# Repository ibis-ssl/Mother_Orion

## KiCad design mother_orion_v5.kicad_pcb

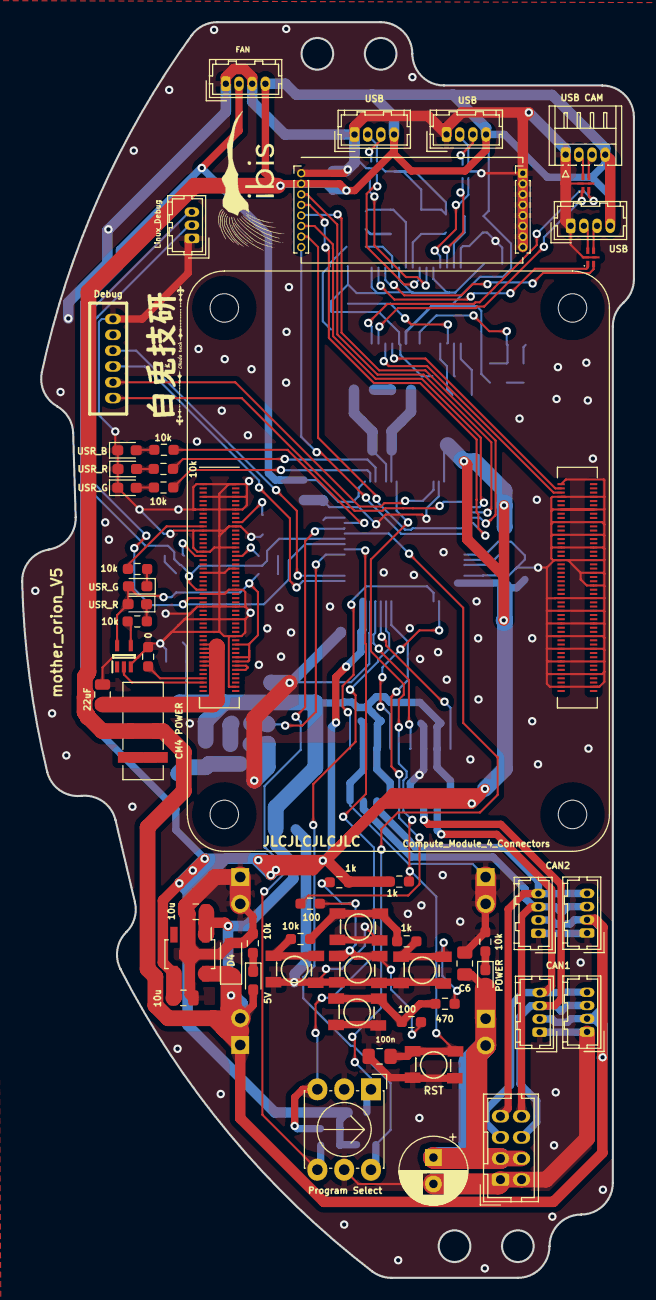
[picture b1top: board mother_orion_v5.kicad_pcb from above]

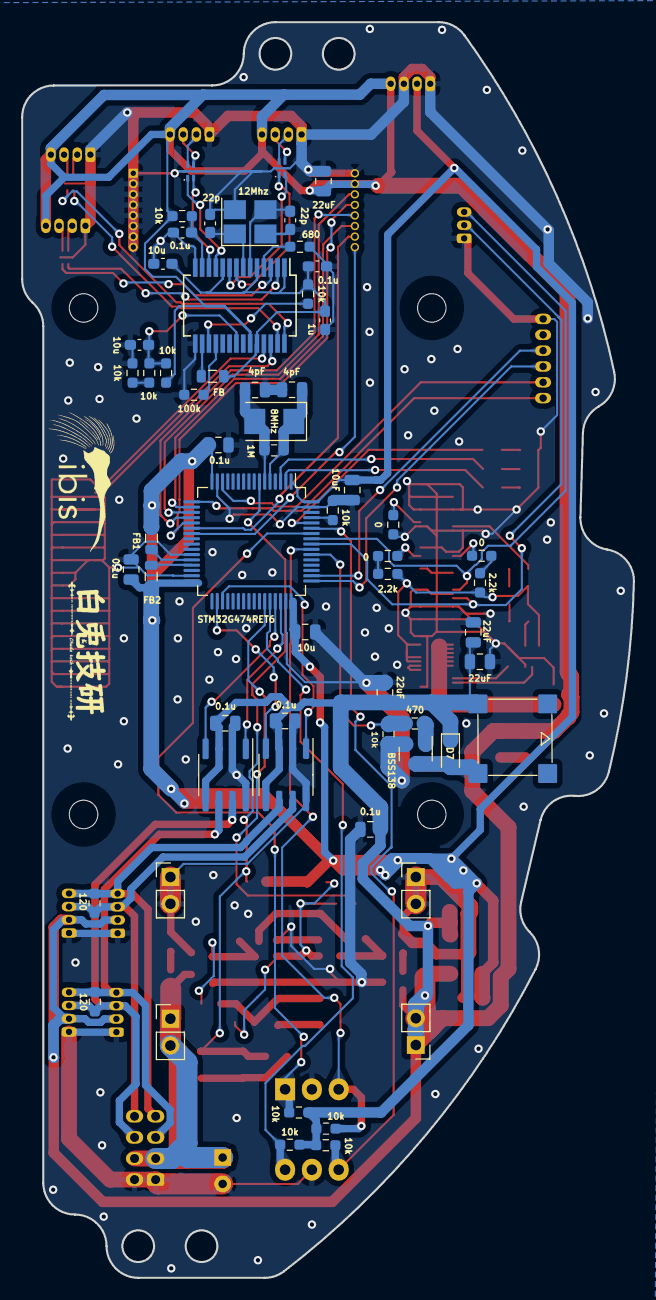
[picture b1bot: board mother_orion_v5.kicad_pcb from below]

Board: 2 copper layers, 58.0 x 119.0 mm, 119 parts (61 on the bottom side), 94 nets.

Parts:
8MHz: Crystal; Crystal_SMD_5032-2Pin_5.0x3.2mm
12Mhz: 12MHz; Crystal_SMD_3225-4Pin_3.2x2.5mm_HandSoldering
 : CAN1_EXT; Hirose_DF13-04P-1.25DSA_1x04_P1.25mm_Vertical
 #2: CAN1_EXT; Hirose_DF13-04P-1.25DSA_1x04_P1.25mm_Vertical
 #3: L_BTN; SW_
 #4,  #23: ibis_logo_mid
 #5: T_BTN; SW_
 #6,  #11: CAN2_EXT; Hirose_DF13-04P-1.25DSA_1x04_P1.25mm_Vertical
 #7: 56uF25V; CP_Radial_D6.3mm_P2.50mm
 #8,  #10,  #21,  #22: LXES11D; FIL_LXES11DAA2-135
 #9: B_BTN; SW_
 #12: Conn_02x04_Odd_Even; Hirose_DF11-8DP-2DSA_2x04_P2.00mm_Vertical
 #13: R_BTN; SW_
 #14,  #17: PinHeader_1x08_P1.00mm_Vertical
 #15: NJM2884U1-33; SOT-89-5
 #16,  #26: sirousagikenn_mini
 #18: 74LVC1G07; SOT65P212X110-5N
 #19: C_BTN; SW_
 #20,  #24,  #25,  #27: power; PinHeader_1x02_P2.54mm_Vertical
 #28,  #30: TCAN1051GDRQ1; SOIC-8_3.9x4.9mm_P1.27mm
 #29: SSOP-28_5.3x10.2mm_P0.65mm
C1, C4, C10: 10u; C_0805_2012Metric
C2: 10uF; C_0805_2012Metric
C3, C5, C7, C12, C12#2: 0.1u; C_0805_2012Metric
C6: 22uF; C_0805_2012Metric_Pad1.18x1.45mm_HandSolder
C14: 100n; C_0805_2012Metric_Pad1.18x1.45mm_HandSolder
C15, C16, C16#2, C16#3, C17: 22uF; C_0805_2012Metric
C18, C19: 4pF; C_0805_2012Metric
C20, C21: 22p; C_0603_1608Metric_Pad1.08x0.95mm_HandSolder
C22, C24: 0.1u; C_0603_1608Metric_Pad1.08x0.95mm_HandSolder
C23, C26: 10u; C_0603_1608Metric_Pad1.08x0.95mm_HandSolder
C25: 1u; C_0603_1608Metric_Pad1.08x0.95mm_HandSolder
CM4 POWER: SW_DPDT_x2; SW_DPDT_CK_JS202011JCQN
D2: 5V; LED_0603_1608Metric_Pad1.05x0.95mm_HandSolder
D3: USR_B; LED_0603_1608Metric_Pad1.05x0.95mm_HandSolder
D4: 5.6V; D_SOD-123
D5, D8: USR_G; LED_0603_1608Metric_Pad1.05x0.95mm_HandSolder
D6, D9: USR_R; LED_0603_1608Metric_Pad1.05x0.95mm_HandSolder
D7: D; D_SOD-323_HandSoldering
FB, FB1, FB2: 600R@100MHz; L_0805_2012Metric
J10: Linux_Debug; Hirose_DF13-03P-1.25DSA_1x03_P1.25mm_Vertical
J11: USB CAM; Hirose_DF13-04P-1.25DS_1x04_P1.25mm_Horizontal
J13: Debug; ZH_6T
J14: FAN; Hirose_DF13-04P-1.25DSA_1x04_P1.25mm_Vertical
POWER: PWR; LED_0603_1608Metric_Pad1.05x0.95mm_HandSolder
Program Select: SW_Coded_SH-7050; Nidec_Copal_SH-7010C
Q1: BSS138; SOT-23
R1, R3, R4, R5, R7, R9, R13, R19, R20, R22, R23, R24, R25, R26, R27, R28, R34, R35, R36: 10k; R_0603_1608Metric_Pad0.98x0.95mm_HandSolder
R2, R6: 120; R_0603_1608Metric_Pad0.98x0.95mm_HandSolder
R8, R12, R17: 1k; R_0603_1608Metric_Pad0.98x0.95mm_HandSolder
R10, R14: 470; R_0603_1608Metric_Pad0.98x0.95mm_HandSolder
R11, R15: 100; R_0603_1608Metric_Pad0.98x0.95mm_HandSolder
R16, R31: 2.2k; R_0603_1608Metric_Pad0.98x0.95mm_HandSolder
R18, R21, R29, R30: 0; R_0603_1608Metric_Pad0.98x0.95mm_HandSolder
R32: 1M; R_0603_1608Metric_Pad0.98x0.95mm_HandSolder
R33: 100k; R_0603_1608Metric_Pad0.98x0.95mm_HandSolder
R37: 680; R_0603_1608Metric_Pad0.98x0.95mm_HandSolder
RST: nRST; SW_
U2: STM32G474RET6; LQFP-64_10x10mm_P0.5mm
U3: Compute_Module_4_Connectors; Raspberry-Pi-4-Compute-Module
USB: USB2.0; Hirose_DF13-04P-1.25DSA_1x04_P1.25mm_Vertical
USB#2, USB#3: USB2.0; Hirose_DF13-04P-1.25DSA_1x04_P1.25mm_Vertical

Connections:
+1V8: U3.88 (CM4_1.8V_Out), U3.90 (CM4_1.8V_Out)
+3.3VA: #18.5 (VCC), D8.2 (A), D9.2 (A), R16.2, R31.2, U3.78 (GPIO_VREF), U3.84 (CM4_3.3V_Out), U3.86 (CM4_3.3V_Out)
+3V3: #15.4 (VOUT), C1.1, C2.1, C3.1, C7.1, C10.1, FB1.2, FB2.2, J14.2, R12.1, R17.1, R24.1, R25.1, R26.1, R27.1, U2.1 (VBAT), U2.16 (VDD), U2.32 (VDD), U2.48 (VDD), U2.64 (VDD)
+5V: .2, #2.2, #6.2, #11.2, #14.2, #15.1 (CTRL), #15.5 (VIN), #25.1, #25.2, #28.3 (VCC), #28.5 (NC), #29.23 (V5), #30.3 (VCC), #30.5 (NC), C4.1, C5.1, C12.1, C12#2.1, C15.1, C16#2.1, C16#3.1, C17.1, CM4 POWER.2 (B), CM4 POWER.5 (B), D2.2 (A), D4.1 (A1), D7.1 (K), J11.4, J14.4, R22.1, R36.2, USB.4, USB#2.4, USB#3.4
+BATT: #7.1, #12.3, #12.4, #20.1, #20.2, C6.1, POWER.2 (A)
/CM4_RX: J10.3, U2.57 (PB4), U3.51 (GPIO15)
/CM4_TX: J10.2, U2.56 (PB3), U3.55 (GPIO14)
/DIP_0: Program Select.1, R24.2, U2.58 (PB5)
/DIP_1: Program Select.2, R25.2, U2.59 (PB6)
/DIP_2: Program Select.4, R26.2, U2.55 (PD2)
/DIP_3: Program Select.8, R27.2, U2.44 (PA10)
/IMU_FSYNC: #14.8, U2.23 (PC5)
/IMU_INT: #14.7, U2.22 (PC4)
/LED_B: R4.2, U2.60 (PB7)
/LED_G: R7.2, U2.2 (PC13)
/LED_R: R9.2, U2.3 (OSC32_IN-PC14)
/SCD1: R30.2, R31.1
/SCL1: R16.1, R18.2
/SPI_IMU_CS: #14.6, U2.18 (PA4)
/SPI_MISO: #14.5, U2.20 (PA6)
/SPI_MOSI: #14.4, U2.21 (PA7)
/SPI_SCLK: #14.3, U2.19 (PA5)
/STLK_RX: J13.6, U2.17 (PA3)
/STLK_TX: J13.5, U2.14 (PA2)
/T_NRST: C14.1, R17.2, RST.2, U2.7 (NRST-PG10)
/T_TCK: J13.3, U2.50 (PA14)
/T_TMS: J13.4, U2.49 (PA13)
/U_BTN: R15.1, U2.43 (PA9)
Buzzer: R13.2, R14.2, U2.54 (PC12)
CAN1_H: .3, #2.3, #12.6, #28.7 (CANH), R2.1
CAN1_L: .4, #2.4, #12.5, #28.6 (CANL), R2.2
CAN1_RXD: #28.4 (RXD), U2.45 (PA11)
CAN1_TXD: #28.1 (TXD), U2.46 (PA12)
CAN2_H: #6.3, #11.3, #12.8, #30.7 (CANH), R6.1
CAN2_L: #6.4, #11.4, #12.7, #30.6 (CANL), R6.2
CAN2_RXD: #30.4 (RXD), U2.34 (PB12)
CAN2_TXD: #30.1 (TXD), U2.35 (PB13)
GND: 12Mhz.2, 12Mhz.4, .1, #2.1, #3.1, #5.1, #6.1, #7.2, #8.3, #8.6, #9.1, #10.3, #10.6, #11.1, #12.1, #12.2, #13.1, #14.1, #15.2 (GND), #17.1, #17.2, #17.3, #17.4, #17.5, #17.6, #17.7, #17.8, #18.3 (GND), #19.1, #21.3, #21.6, #22.3, #22.6, #24.1, #24.2, #27.1, #27.2, #28.2 (GND), #28.8 (S), #29.14 (TEST), #29.15 (GND), #30.2 (GND), #30.8 (S), C1.2, C2.2, C3.2, C4.2, C5.2, C6.2, C7.2, C10.2, C12.2, C12#2.2, C14.2, C15.2, C16.1, C16#2.2, C16#3.2, C17.2, C18.1, C19.2, C20.2, C21.2, C22.2, C23.2, C24.2, C25.2, C26.2, D3.1 (K), D4.2 (A2), D5.1 (K), D6.1 (K), J10.1, J11.1, J13.1, J14.1, J14.3, Program Select.C, Q1.2 (S), R1.1, R3.1, R13.1, R21.1, R28.1, R29.2, R33.2, R34.1, R37.1, RST.1, U2.15 (VSS), U2.27 (VSSA), U2.31 (VSS), U2.47 (VSS), U2.63 (VSS), U3.1 (GND), U3.2 (GND), U3.7 (GND), U3.8 (GND), U3.13 (GND), U3.14 (GND), U3.22 (GND), U3.23 (GND), U3.32 (GND), U3.33 (GND), U3.42 (GND), U3.43 (GND), U3.52 (GND), U3.53 (GND), U3.59 (GND), U3.60 (GND), U3.65 (GND), U3.66 (GND), U3.71 (GND), U3.74 (GND), U3.98 (GND), U3.101 (USB_OTG_ID), U3.107 (GND), U3.108 (GND), U3.113 (GND), U3.114 (GND), U3.119 (GND), U3.120 (GND), U3.125 (GND), U3.126 (GND), U3.131 (GND), U3.132 (GND), U3.137 (GND), U3.138 (GND), U3.144 (GND), U3.150 (GND), U3.155 (GND), U3.156 (GND), U3.161 (GND), U3.162 (GND), U3.167 (GND), U3.168 (GND), U3.173 (GND), U3.174 (GND), U3.179 (GND), U3.180 (GND), U3.185 (GND), U3.186 (GND), U3.191 (GND), U3.192 (GND), U3.197 (GND), U3.198 (GND), USB.1, USB#2.1, USB#3.1
unnamed: #19.2, R11.1, R12.2, R15.2
unnamed: POWER.1 (K), R1.2
unnamed: D2.1 (K), R3.2
unnamed: D3.2 (A), R4.1
unnamed: D5.2 (A), R7.1
unnamed: D6.2 (A), R9.1
unnamed: D7.2 (A), Q1.3 (D)
unnamed: D8.1 (K), R19.1
unnamed: D9.1 (K), R20.1
unnamed: #8.5, J11.2
unnamed: #8.4, J11.3
unnamed: #10.5, USB.2
unnamed: #10.4, USB.3
unnamed: #21.5, USB#3.2
unnamed: #21.4, USB#3.3
unnamed: #22.5, USB#2.2
unnamed: #22.4, USB#2.3
unnamed: Q1.1 (G), R14.1
unnamed: #5.2, R5.1, R8.2
unnamed: #3.2, R5.2
unnamed: #9.2, R10.1, R11.2
unnamed: #13.2, R8.1, R10.2
unnamed: #18.4, R20.2
unnamed: R34.2, R35.1
unnamed: C16.2, CM4 POWER.1 (A), CM4 POWER.4 (A), U3.77 (+5V), U3.79 (+5V), U3.81 (+5V), U3.83 (+5V), U3.85 (+5V), U3.87 (+5V)
unnamed: CM4 POWER.3 (C), CM4 POWER.6 (C)
unnamed: 8MHz.1, C18.2, R32.1, U2.5 (OSC_IN-PF0)
unnamed: 8MHz.2, C19.1, R32.2, U2.6 (OSC_OUT-PF1)
unnamed: R28.2, U2.61 (PB8-BOOT0)
unnamed: R29.1, U3.20 (EEPROM_nWP)
unnamed: R18.1, U3.35 (ID_SC)
unnamed: R30.1, U3.36 (ID_SD)
unnamed: #18.2, U3.95 (~PI_LED_nPWR)
unnamed: R19.2, U3.21 (~Pi_nLED_Activity)
unnamed: R21.2, U3.93 (~nRPIBOOT)
unnamed: #29.16 (DVDD), FB.2
unnamed: #29.21 (OVCR1#), C26.1, R35.2, R36.1
unnamed: #29.18 (PGAND), R33.1
unnamed: #29.17 (PSELF), R23.1
unnamed: #29.4 (RREF), R37.2
unnamed: #29.13 (RST#), C22.1, R22.2
unnamed: #29.1 (AVDD), #29.5 (AVDD), #29.10 (AVDD), #29.24 (V33), C23.1, C24.1, C25.1, FB.1, R23.2
unnamed: 12Mhz.3, #29.6 (X1), C20.1
unnamed: 12Mhz.1, #29.7 (X2), C21.1
USB_DM: #29.25 (DM0), U3.103 (USB_N)
USB_DM0: #8.1, #29.27 (DM1)
USB_DM1: #10.1, #29.2 (DM2)
USB_DM2: #21.1, #29.8 (DM3)
USB_DM3: #22.1, #29.11 (DM4)
USB_DP: #29.26 (DP0), U3.105 (USB_P)
USB_DP0: #8.2, #29.28 (DP1)
USB_DP1: #10.2, #29.3 (DP2)
USB_DP2: #21.2, #29.9 (DP3)
USB_DP3: #22.2, #29.12 (DP4)
VDDA: FB2.1, U2.29 (VDDA)
VDDF: FB1.1, U2.28 (VREF+)

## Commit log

2024-10-14 1st commit
